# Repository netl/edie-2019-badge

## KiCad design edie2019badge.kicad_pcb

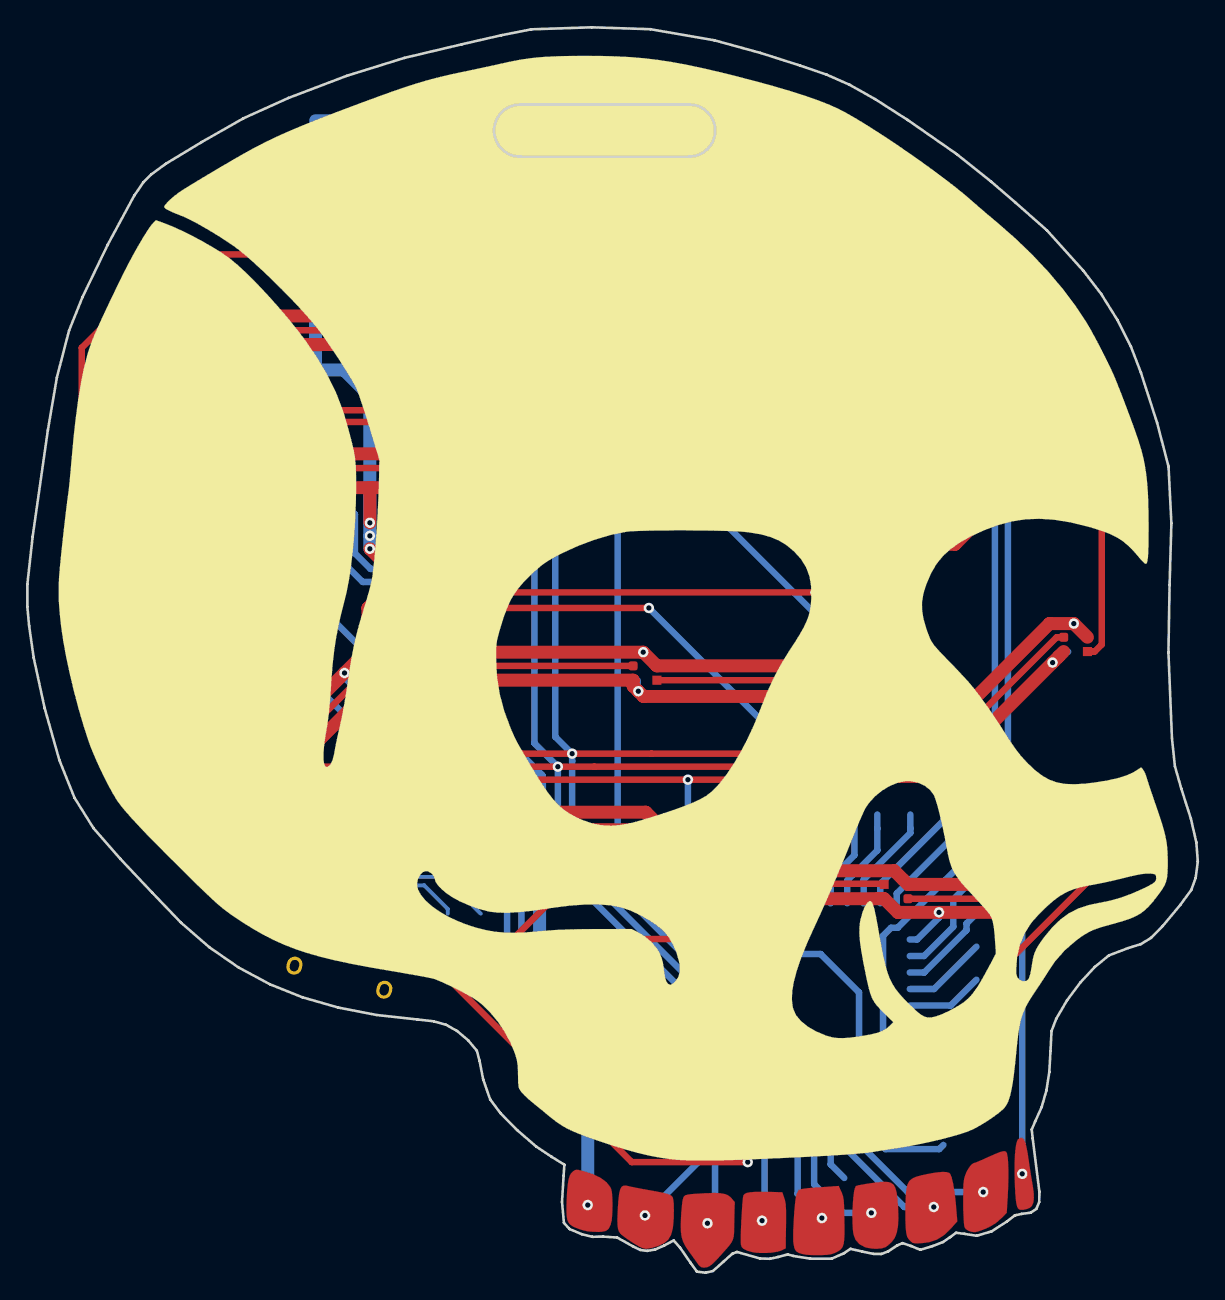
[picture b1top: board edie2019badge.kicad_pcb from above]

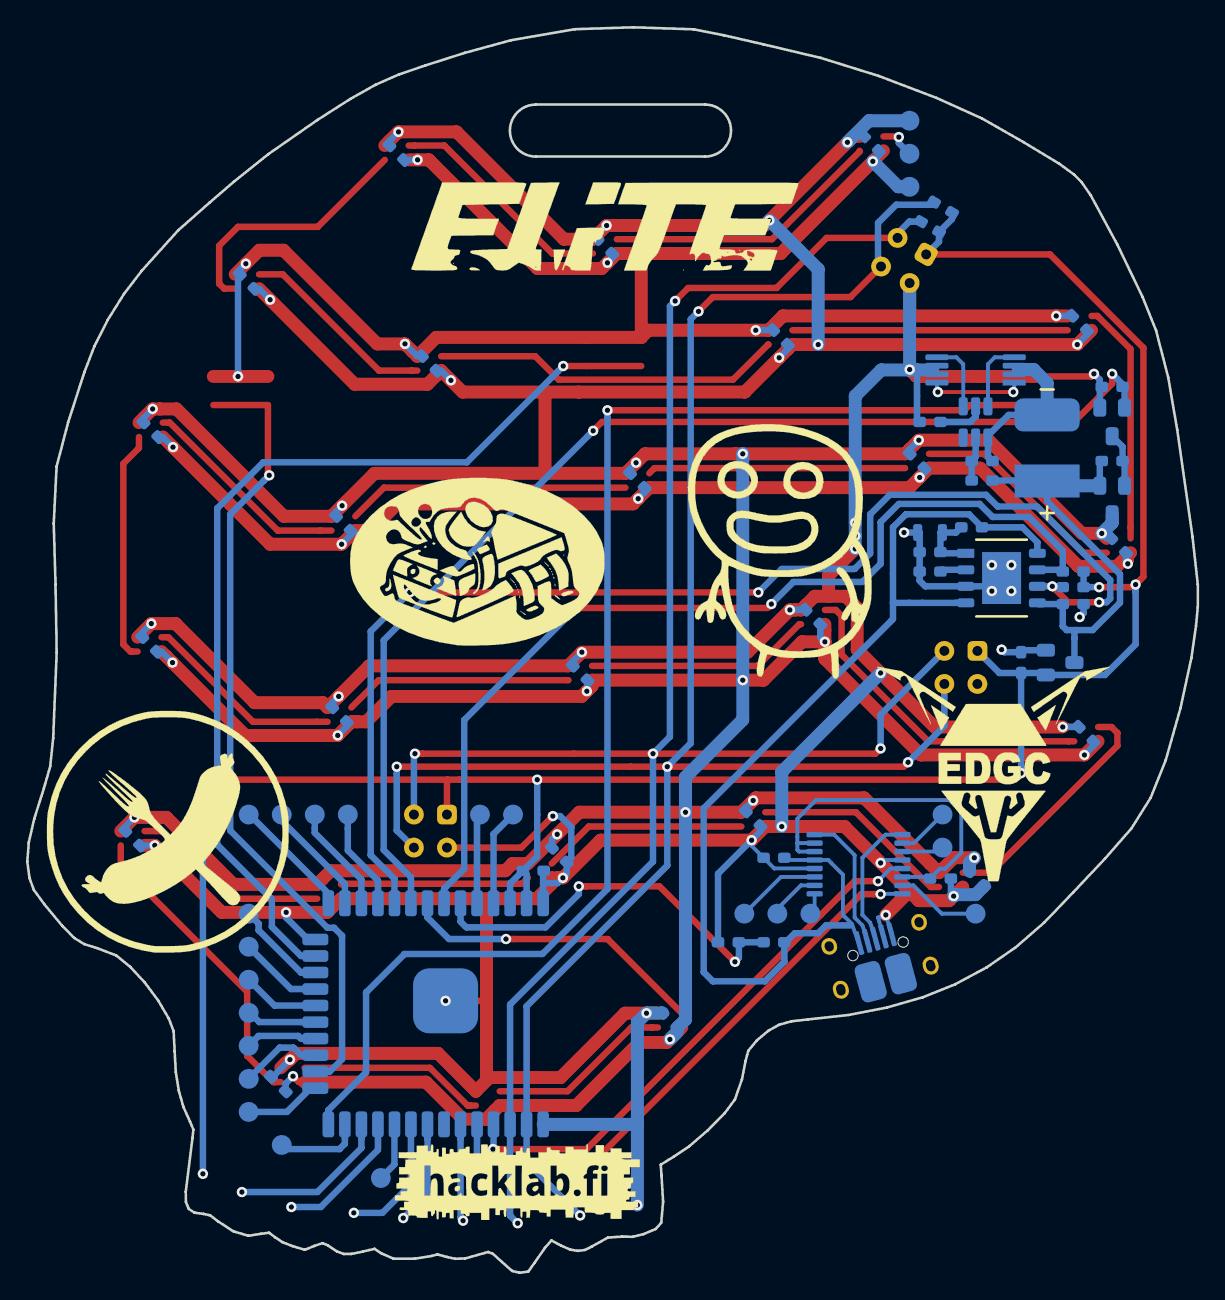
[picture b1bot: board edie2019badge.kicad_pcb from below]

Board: 2 copper layers, 90.0 x 95.7 mm, 109 parts (77 on the bottom side), 80 nets.

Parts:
BAT1: Battery; battery_wires
C1, C2, C3, C4, C6, C7, C8, C9, C10, C11, C12, C14, C15, C16, C17, C18, C19, C20, C21, C22, C23, C24, C25, C26, C27, C28, C29, C30, C31: C; 0603
CN1: USB-Micro; micro_usb
CN2, CN3, CN4: 2x2
D1, D2, D3, D4, D5, D6, D7, D8, D9, D10, D11, D12, D13, D14, D15, D16, D17, D18, D19, D20, D21, D22, D23, D24, D25: WS2812B; 2020
IC1: ESP-32-WROOM; ESP-23-WROOM
IC2: XC6206P332MR; SOT-23
IC3: TP4056; SOP-8
IC4: DW01; SOT-23-6
IC5: FT230XS; SSOP-16
R1, R2, R3, R4, R5, R6, R7, R8, R9, R11, R12, R13, R14: R; 0603
R10: R; 0805
SKL666: Skull; skull
SW1, SW2, SW3: switch_3x4; sw_3x4
T1: AO3401; SOT-23
T2: AO3400; SOT-23
T3: FS8205A; TSSOP-8
TP1, TP2, TP3, TP4, TP5, TP6, TP7, TP8, TP9, TP11, TP12, TP13, TP14, TP15, TP16, TP17, TP18, TP19, TP20, TP21, TP22, TP23, TP24, TP25: test_point

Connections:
+3V3: C1.1, C2.1, CN2.1, CN3.1, CN4.1, IC1.2, IC1.3, IC2.2, R4.1, R6.1, R7.1, R13.1, SKL666.9
+5V_USB: C11.1, CN1.1, IC3.4, IC3.8, IC5.12, R1.1, R8.1
/LED strip/+V_LEDs: C3.1, C4.1, C6.1, C7.1, C8.1, C14.1, C15.1, C16.1, C17.1, C18.1, C19.1, C20.1, C21.1, C22.1, C23.1, C24.1, C25.1, C26.1, C27.1, C28.1, C29.1, C30.1, C31.1, D1.4, D2.4, D3.4, D4.4, D5.4, D6.4, D7.4, D8.4, D9.4, D10.4, D11.4, D12.4, D13.4, D14.4, D15.4, D16.4, D17.4, D18.4, D19.4, D20.4, D21.4, D22.4, D23.4, D24.4, D25.4, T1.3, TP18.1
/LED strip/LED_strip_data: D1.3, IC1.8
/LED strip/LED_strip_enable: IC1.9, R14.1, T2.1
/USB interface/RX: IC1.34, IC5.1
/USB interface/TX: IC1.35, IC5.4
/USB interface/USBN: CN1.2, IC5.9
/USB interface/USBP: CN1.3, IC5.8
/USB interface/USB_power: IC1.6, R1.2, R2.1
/esp32/MISO: IC1.31, SKL666.5
/esp32/MOSI: IC1.33, SKL666.4
/esp32/RX2: IC1.27, SKL666.8
/esp32/SCK: IC1.30, SKL666.6
/esp32/SCL: CN2.4, CN3.4, CN4.4, IC1.37, R6.2, SKL666.2
/esp32/SDA: CN2.2, CN3.2, CN4.2, IC1.36, R7.2, SKL666.3
/esp32/TX2: IC1.28, SKL666.7
/esp32/button_left: IC1.25, SW1.1, SW1.2
/esp32/button_mid: IC1.16, SW2.1, SW2.2
/esp32/button_right: IC1.23, SW3.1, SW3.2
/esp32/~battery_charging: IC1.7, IC3.7, R4.2
/esp32/~battery_standby: IC1.10, IC3.6, R13.2
GND: C1.2, C2.2, C3.2, C4.2, C6.2, C7.2, C8.2, C9.2, C11.2, C12.2, C14.2, C15.2, C16.2, C17.2, C18.2, C19.2, C20.2, C21.2, C22.2, C23.2, C24.2, C25.2, C26.2, C27.2, C28.2, C29.2, C30.2, C31.2, CN1.4, CN1.5, CN2.3, CN3.3, CN4.3, D1.2, D2.2, D3.2, D4.2, D5.2, D6.2, D7.2, D8.2, D9.2, D10.2, D11.2, D12.2, D13.2, D14.2, D15.2, D16.2, D17.2, D18.2, D19.2, D20.2, D21.2, D22.2, D23.2, D24.2, D25.2, IC1.1, IC1.15, IC1.38, IC1.39, IC2.1, IC3.0, IC3.3, IC5.5, IC5.13, R2.2, R5.2, R9.2, R10.2, R12.2, R14.2, SKL666.1, SW1.3, SW1.4, SW2.3, SW2.4, SW3.3, SW3.4, T2.2, T3.6, T3.7, TP19.1
unnamed: BAT1.2, C10.2, IC4.6, T3.2, T3.3
unnamed: C10.1, IC4.5, R11.2
unnamed: C12.1, IC5.3, IC5.10, IC5.11
unnamed: D1.1, D2.3
unnamed: D2.1, D3.3
unnamed: D3.1, D4.3
unnamed: D4.1, D5.3
unnamed: D5.1, D6.3
unnamed: D6.1, D7.3
unnamed: D7.1, D8.3
unnamed: D8.1, D9.3
unnamed: D10.1, D11.3
unnamed: D9.1, D10.3
unnamed: D11.1, D12.3
unnamed: D12.1, D13.3
unnamed: D13.1, D14.3
unnamed: D14.1, D15.3
unnamed: D15.1, D16.3
unnamed: D16.1, D17.3
unnamed: D17.1, D18.3
unnamed: D18.1, D19.3
unnamed: D19.1, D20.3
unnamed: D20.1, D21.3
unnamed: D21.1, D22.3
unnamed: D22.1, D23.3
unnamed: D23.1, D24.3
unnamed: D24.1, D25.3
unnamed: D25.1, TP1.1
unnamed: IC1.4, TP2.1
unnamed: IC1.5, TP3.1
unnamed: IC1.11, TP11.1
unnamed: IC1.12, TP12.1
unnamed: IC1.13, TP16.1
unnamed: IC1.14, TP15.1
unnamed: IC1.17, TP4.1
unnamed: IC1.18, TP5.1
unnamed: IC1.19, TP6.1
unnamed: IC1.20, TP7.1
unnamed: IC1.21, TP8.1
unnamed: IC1.22, TP9.1
unnamed: IC1.24, TP14.1
unnamed: IC1.26, TP13.1
unnamed: IC1.29, TP17.1
unnamed: IC3.1, R8.2, R9.1, R10.1
unnamed: IC3.2, R5.1
unnamed: IC4.1, T3.4
unnamed: IC4.2, R12.1
unnamed: IC4.3, T3.5
unnamed: IC5.2, TP20.1
unnamed: IC5.6, TP21.1
unnamed: IC5.7, TP24.1
unnamed: IC5.14, TP23.1
unnamed: IC5.15, TP22.1
unnamed: IC5.16, TP25.1
unnamed: R3.2, T1.1, T2.3
unnamed: T3.1, T3.8
VCC: BAT1.1, C9.1, IC2.3, IC3.5, R3.1, R11.1, T1.2

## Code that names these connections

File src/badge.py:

class badge():
    from machine import Pin, unique_id, I2C
    from neopixel import NeoPixel

    print("start")

    identity = unique_id()

    #buttons
    print("buttons")
    button_left = Pin(0, Pin.IN, Pin.PULL_UP)
    button_mid = Pin(13, Pin.IN, Pin.PULL_UP)
    button_right = Pin(15, Pin.IN, Pin.PULL_UP)

    #led power switch
    print("led power switch")
    led_power = Pin(33, Pin.OUT)
    led_power.off()

    #usb/battery status
    print("battery status")
    usb_power = Pin(34, Pin.IN)
    battery_charging = Pin(35, Pin.IN)
    battery_standby = Pin(25, Pin.IN)

    #i2c
    print("i2c")
    i2c = I2C(scl=Pin(23), sda=Pin(22), freq=100000)

    #neopixels
    #https://learn.adafruit.com/led-tricks-gamma-correction/the-quick-fix
    print("neopixel")
    gamma = [
        0,  0,  0,  0,  0,  0,  0,  0,  0,  0,  0,  0,  0,  0,  0,  0,
        0,  0,  0,  0,  0,  0,  0,  0,  0,  0,  0,  0,  1,  1,  1,  1,
        1,  1,  1,  1,  1,  1,  1,  1,  1,  2,  2,  2,  2,  2,  2,  2,
        2,  3,  3,  3,  3,  3,  3,  3,  4,  4,  4,  4,  4,  5,  5,  5,
        5,  6,  6,  6,  6,  7,  7,  7,  7,  8,  8,  8,  9,  9,  9, 10,
       10, 10, 11, 11, 11, 12, 12, 13, 13, 13, 14, 14, 15, 15, 16, 16,
       17, 17, 18, 18, 19, 19, 20, 20, 21, 21, 22, 22, 23, 24, 24, 25,
       25, 26, 27, 27, 28, 29, 29, 30, 31, 32, 32, 33, 34, 35, 35, 36,
       37, 38, 39, 39, 40, 41, 42, 43, 44, 45, 46, 47, 48, 49, 50, 50,
       51, 52, 54, 55, 56, 57, 58, 59, 60, 61, 62, 63, 64, 66, 67, 68,
       69, 70, 72, 73, 74, 75, 77, 78, 79, 81, 82, 83, 85, 86, 87, 89,
       90, 92, 93, 95, 96, 98, 99,101,102,104,105,107,109,110,112,114,
      115,117,119,120,122,124,126,127,129,131,133,135,137,138,140,142,
      144,146,148,150,152,154,156,158,160,162,164,167,169,171,173,175,
      177,180,182,184,186,189,191,193,196,198,200,203,205,208,210,213,
      215,218,220,223,225,228,231,233,236,239,241,244,247,249,252,255
      ]
    #Pin(32, Pin.IN)
    #np = NeoPixel(Pin(26),25)
    np = NeoPixel(Pin(32),25)
    #TODO figure out how many leds are attached

    class pixel():
        def __init__(self,x,y,np_id):
            self.x = x
            self.y = y 
            self.np_id = np_id

        def get_rgb(self):
            return badge.np[self.np_id]

        def set_rgb(self, rgb = (0,0,0)):
            badge.np[self.np_id] = (
                badge.gamma[int(rgb[0]*255)],
                badge.gamma[int(rgb[1]*255)],
                badge.gamma[int(rgb[2]*255)]
                )

    #array of pixels with their coordinates on the badge
    print("creating pixels")
    pixels = []
    i = 0
    for pos in [[-0.09, -0.842], [0.28, -1.0], [0.675, -0.953], [1.0, -0.472], [0.602, -0.58], [0.174, -0.538], [-0.259, -0.434], [-0.66, -0.557], [-0.934, -0.261], [-0.38, -0.024], [0.092, -0.137], [0.58, -0.222], [0.966, -0.079], [0.963, 0.356], [0.573, 0.166], [-0.024, 0.253], [-0.591, 0.293], [-1.0, 0.121], [-0.921, 0.573], [-0.314, 0.544], [0.398, 0.491], [0.768, 0.657], [0.464, 0.918], [0.042, 0.728], [-0.499, 0.937]]:
        pixels.append(pixel(pos[0],pos[1],i))
        i += 1

    print("done")

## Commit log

2019-08-15 added breakout teeth as a component to schematic
2019-08-15 added guesses for uart, i2c and spi pinouts
2019-08-19 added shitty add-on headers and changed lanyard hole shape
2019-08-19 added voltage regulator
2019-08-27 added buttons
2019-08-27 started doing track layout
2019-08-28 tweaked trace layout
2019-08-29 added test points to unused pins
2019-08-29 trace layout complete for now, still missing some footprints
2019-08-29 added pull-ups for i2c, added missing testpoint
2019-09-02 layout completed
2019-09-03 added logos
2019-09-11 added battery charging, tweaked esp32 signals
2019-09-12 changed buttons, tweaked esp32 pinout, added test points for vcc&gnd to led strip
2019-09-12 started reworking layout
2019-09-13 started battery protection circuit layout
2019-09-16 charger layout partially done
2019-09-19 added USB connector
2019-09-19 almost all nets complete in layout
2019-09-19 added more logos
2019-09-23 added game crew logo
2019-09-26 did led strip decoupling capacitor routing
2019-10-01 added battery charging signal
2019-10-03 added bypass capacitors to most of the leds, reworked layout
2019-10-04 layout complete. changed NTC package to 0805
2019-10-04 tweaked branding
2019-10-04 added pull-down for led power signal
2019-10-04 forgot to commit schematic
2019-10-04 added source code
2019-10-04 art-net should disable the default animation
2019-10-05 minor tweak on charger ground pour
2019-10-05 moved signal away from elite dekkerz logo
2019-10-06 added python script for badges as virtual joysticks
2023-03-07 copied working code from badge :D
